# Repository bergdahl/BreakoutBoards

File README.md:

# BreakoutBoards
Prototyping breakout boards

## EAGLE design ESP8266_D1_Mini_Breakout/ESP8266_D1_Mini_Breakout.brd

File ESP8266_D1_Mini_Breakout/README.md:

# Esp8266_D1Mini_Breakout

Work in progress...

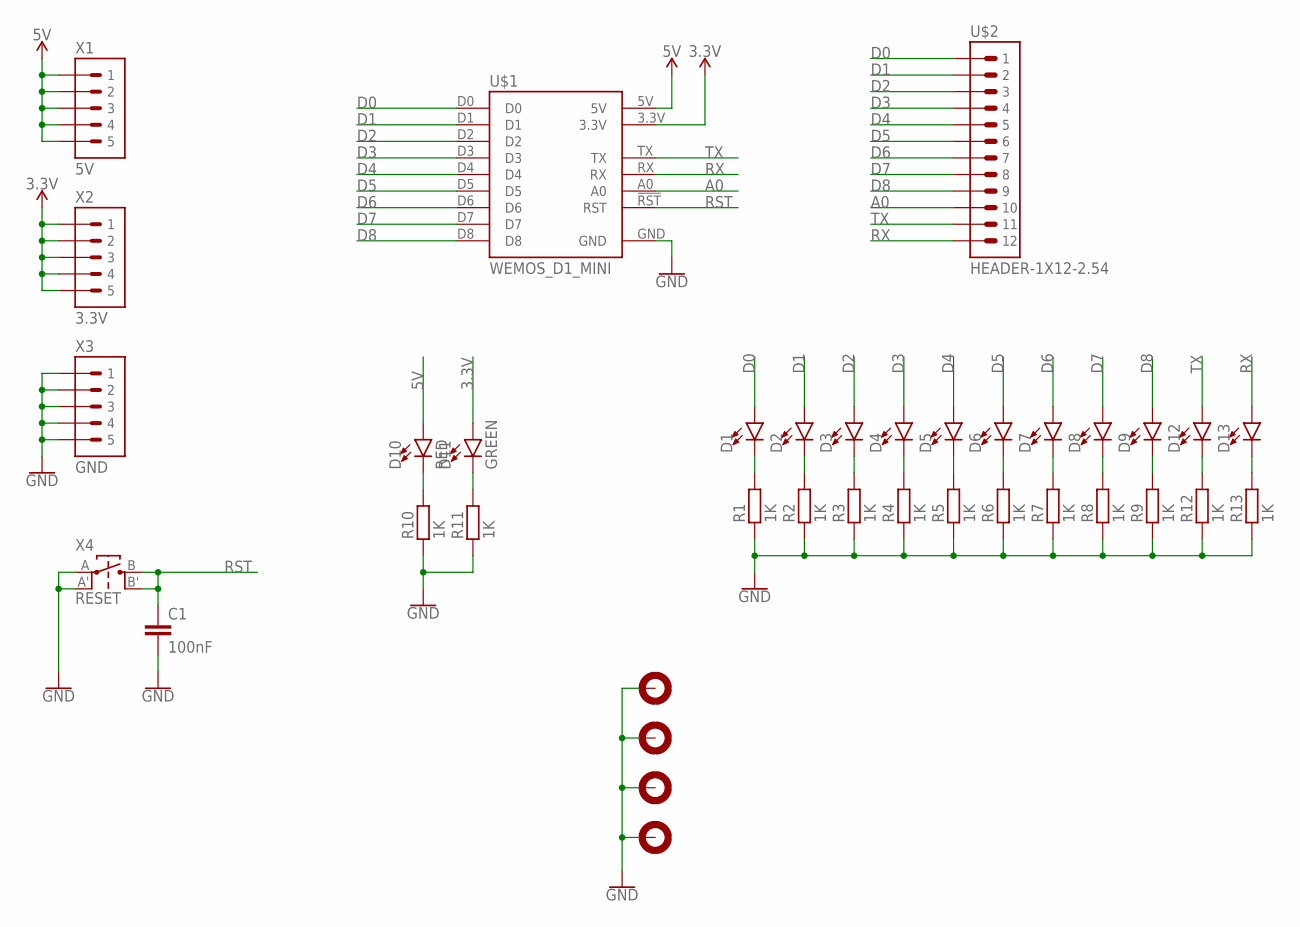
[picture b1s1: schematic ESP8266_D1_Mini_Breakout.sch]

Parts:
C1: 100nF; C0603
D1, D2, D3, D4, D5, D6, D7, D8, D9, D12, D13: LED0603
D10: RED; LED0603
D11: GREEN; LED0603
H1, H2, H3, H4: MOUNTHOLE-PAD3.2; 3.2-PAD
R1, R2, R3, R4, R5, R6, R7, R8, R9, R10, R11, R12, R13: 1K; R0603
U$1: WEMOS_D1_MINI
U$2: HEADER-1X12-2.54; 1X12-2.54
X1: 5V; 1X05-2.54
X2: 3.3V; 1X05-2.54
X3: GND; 1X05-2.54
X4: RESET; TACT-SWITCH-EVQ

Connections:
3.3V: D11.A, U$1.3.3V, X2.1, X2.2, X2.3, X2.4, X2.5
5V: D10.A, U$1.5V, X1.1, X1.2, X1.3, X1.4, X1.5
A0: U$1.A0, U$2.10
D0: D1.A, U$1.D0, U$2.1
D1: D2.A, U$1.D1, U$2.2
D2: D3.A, U$1.D2, U$2.3
D3: D4.A, U$1.D3, U$2.4
D4: D5.A, U$1.D4, U$2.5
D5: D6.A, U$1.D5, U$2.6
D6: D7.A, U$1.D6, U$2.7
D7: D8.A, U$1.D7, U$2.8
D8: D9.A, U$1.D8, U$2.9
GND: C1.2, H1.B3,2, H2.B3,2, H3.B3,2, H4.B3,2, R1.1, R2.1, R3.1, R4.1, R5.1, R6.1, R7.1, R8.1, R9.1, R10.1, R11.1, R12.1, R13.1, U$1.GND, X3.1, X3.2, X3.3, X3.4, X3.5, X4.A, X4.A'
unnamed: D11.C, R11.2
unnamed: D10.C, R10.2
unnamed: D13.C, R13.2
unnamed: D12.C, R12.2
unnamed: D9.C, R9.2
unnamed: D8.C, R8.2
unnamed: D7.C, R7.2
unnamed: D6.C, R6.2
unnamed: D5.C, R5.2
unnamed: D4.C, R4.2
unnamed: D3.C, R3.2
unnamed: D2.C, R2.2
unnamed: D1.C, R1.2
RST: C1.1, U$1.!RST (RST), X4.B, X4.B'
RX: D13.A, U$1.RX, U$2.12
TX: D12.A, U$1.TX, U$2.11

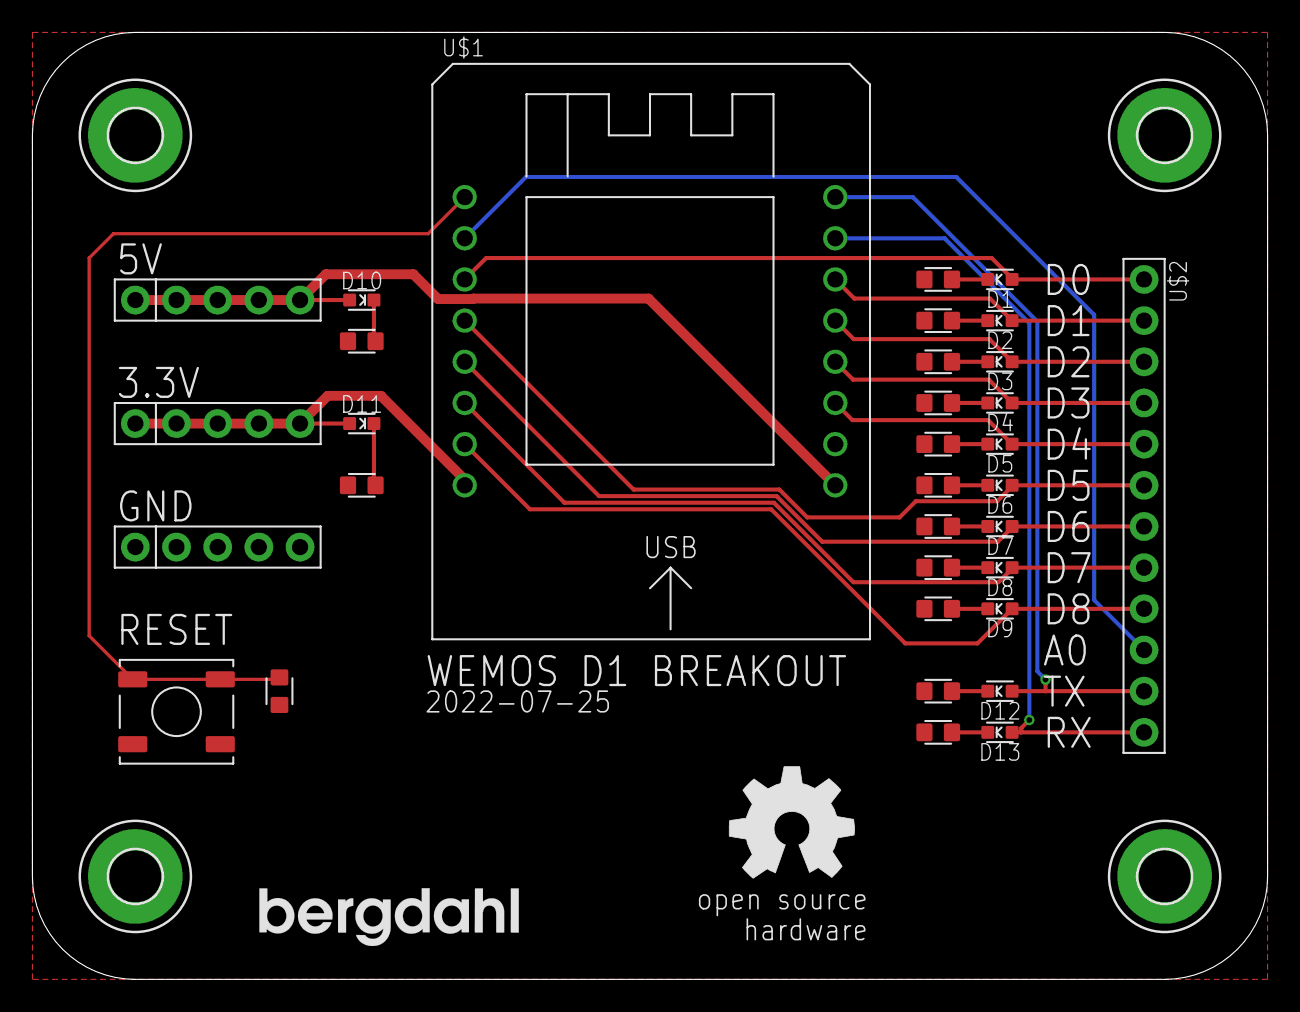
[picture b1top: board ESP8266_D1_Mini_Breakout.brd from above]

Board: 2 copper layers, 76.2 x 58.4 mm, 39 parts (0 on the bottom side), 29 nets.

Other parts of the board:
U$3: BERGDAHL-20MM-TPLACE
U$4: OSHW-8MM-TPLACE

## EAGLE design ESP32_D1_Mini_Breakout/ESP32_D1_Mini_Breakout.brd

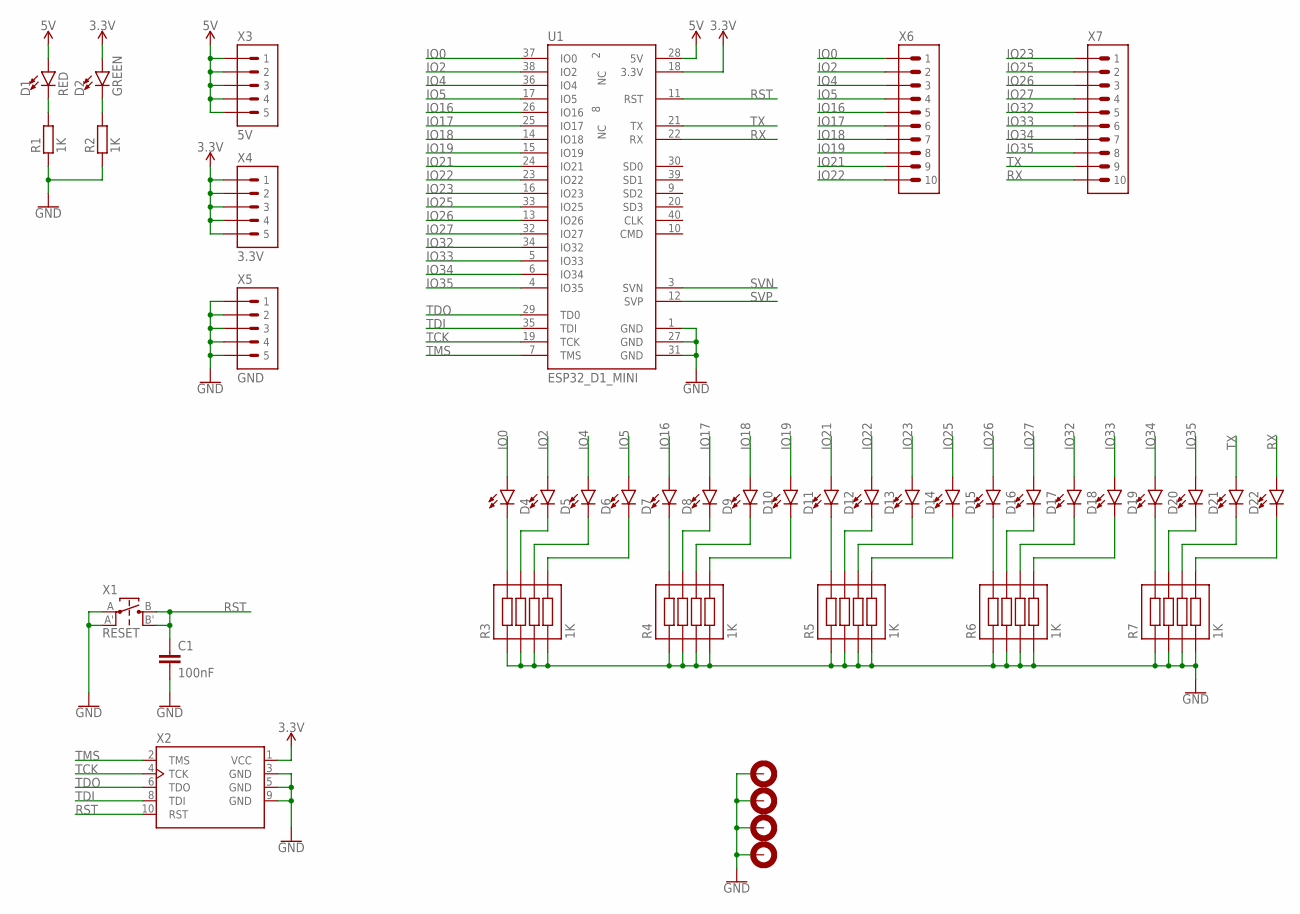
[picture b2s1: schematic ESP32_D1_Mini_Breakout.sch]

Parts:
C1: 100nF; C0603
D1: RED; LED0603
D2: GREEN; LED0603
D3, D4, D5, D6, D7, D8, D9, D10, D11, D12, D13, D14, D15, D16, D17, D18, D19, D20, D21, D22: LED0603
H1, H2, H3, H4: MOUNTHOLE-PAD3.2; 3.2-PAD
R1, R2: 1K; R0603
R3, R4, R5, R6, R7: 1K; RX4_1206
U1: ESP32_D1_MINI; WEMOS_ESP32_D1_MINI
X1: RESET; TACT-SWITCH-EVQ
X2: ESP32-JTAGTH; 2X05-1.27-SWD
X3: 5V; 1X05-2.54
X4: 3.3V; 1X05-2.54
X5: GND; 1X05-2.54
X6, X7: HEADER-1X10-2.54; 1X10-2.54

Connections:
3.3V: D2.A, U1.18 (3.3V), X2.1 (VCC), X4.1, X4.2, X4.3, X4.4, X4.5
5V: D1.A, U1.28 (5V), X3.1, X3.2, X3.3, X3.4, X3.5
GND: C1.2, H1.B3,2, H2.B3,2, H3.B3,2, H4.B3,2, R1.1, R2.1, R3.1, R3.3, R3.5, R3.7, R4.1, R4.3, R4.5, R4.7, R5.1, R5.3, R5.5, R5.7, R6.1, R6.3, R6.5, R6.7, R7.1, R7.3, R7.5, R7.7, U1.1 (GND), U1.27 (GND), U1.31 (GND), X1.A, X1.A', X2.3 (GND), X2.5 (GND), X2.9 (GND), X5.1, X5.2, X5.3, X5.4, X5.5
IO0: D3.A, U1.37 (IO0), X6.1
IO2: D4.A, U1.38 (IO2), X6.2
IO4: D5.A, U1.36 (IO4), X6.3
IO5: D6.A, U1.17 (IO5), X6.4
IO16: D7.A, U1.26 (IO16), X6.5
IO17: D8.A, U1.25 (IO17), X6.6
IO18: D9.A, U1.14 (IO18), X6.7
IO19: D10.A, U1.15 (IO19), X6.8
IO21: D11.A, U1.24 (IO21), X6.9
IO22: D12.A, U1.23 (IO22), X6.10
IO23: D13.A, U1.16 (IO23), X7.1
IO25: D14.A, U1.33 (IO25), X7.2
IO26: D15.A, U1.13 (IO26), X7.3
IO27: D16.A, U1.32 (IO27), X7.4
IO32: D17.A, U1.34 (IO32), X7.5
IO33: D18.A, U1.5 (IO33), X7.6
IO34: D19.A, U1.6 (IO34), X7.7
IO35: D20.A, U1.4 (IO35), X7.8
unnamed: D2.C, R2.2
unnamed: D1.C, R1.2
unnamed: D6.C, R3.8
unnamed: D5.C, R3.6
unnamed: D4.C, R3.4
unnamed: D3.C, R3.2
unnamed: D7.C, R4.2
unnamed: D8.C, R4.4
unnamed: D9.C, R4.6
unnamed: D10.C, R4.8
unnamed: D11.C, R5.2
unnamed: D12.C, R5.4
unnamed: D13.C, R5.6
unnamed: D14.C, R5.8
unnamed: D15.C, R6.2
unnamed: D16.C, R6.4
unnamed: D18.C, R6.8
unnamed: D17.C, R6.6
unnamed: D19.C, R7.2
unnamed: D20.C, R7.4
unnamed: D21.C, R7.6
unnamed: D22.C, R7.8
RST: C1.1, U1.11 (RST), X1.B, X1.B', X2.10 (RST)
RX: D22.A, U1.22 (RX), X7.10
SVN: U1.3 (SVN)
SVP: U1.12 (SVP)
TCK: U1.19 (TCK), X2.4 (TCK)
TDI: U1.35 (TDI), X2.8 (TDI)
TDO: U1.29 (TD0), X2.6 (TDO)
TMS: U1.7 (TMS), X2.2 (TMS)
TX: D21.A, U1.21 (TX), X7.9

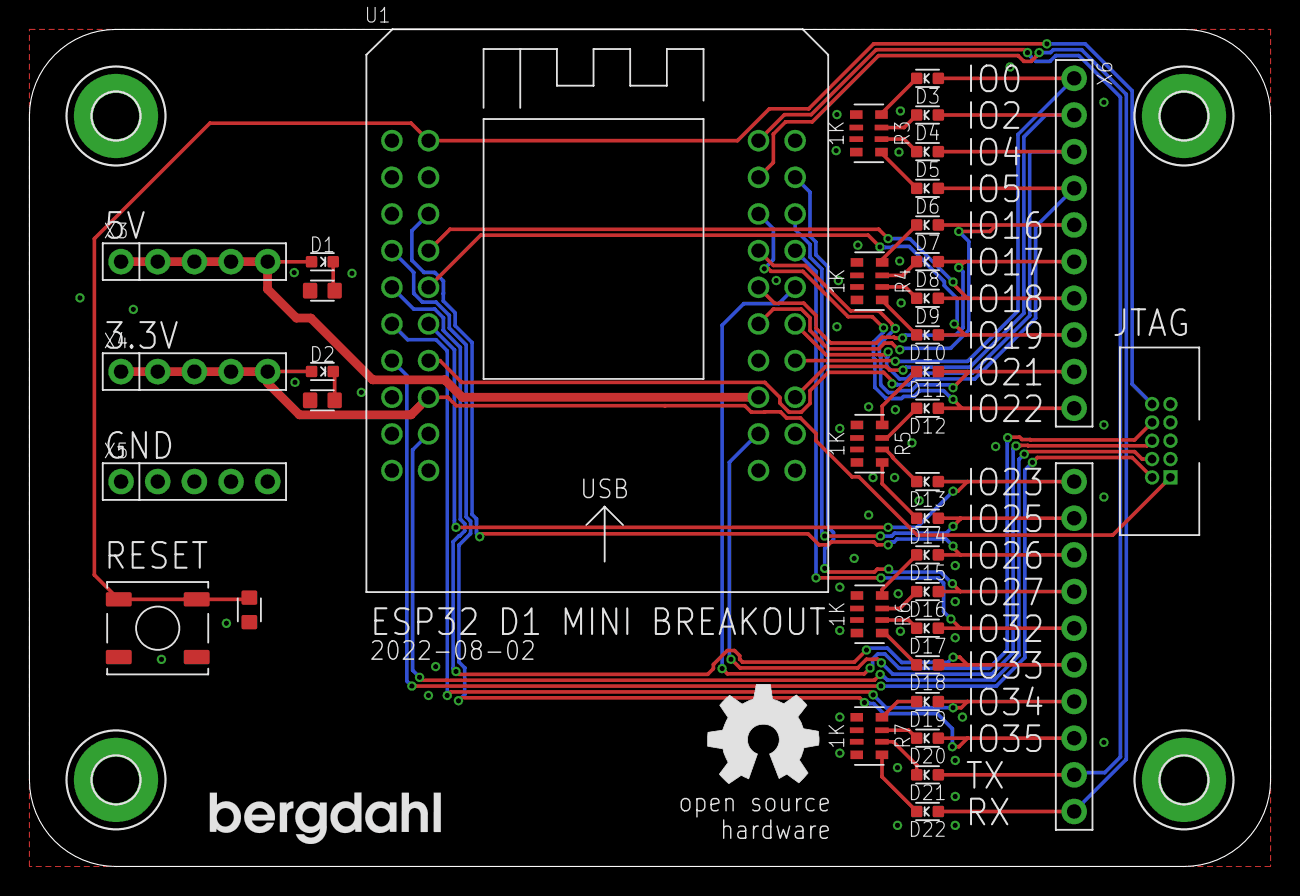
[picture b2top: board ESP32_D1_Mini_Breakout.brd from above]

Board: 2 copper layers, 86.0 x 58.0 mm, 44 parts (0 on the bottom side), 50 nets.

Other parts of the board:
U$3: BERGDAHL-20MM-TPLACE
U$4: OSHW-8MM-TPLACE

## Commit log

2022-08-02 Done routing Add Gerber files
